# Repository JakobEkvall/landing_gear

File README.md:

# landing_gear
PCB for the Shafter quadrotor landing platforms stepper motor and limit switches. 

Schematics and PCB designed with KiCad. 

Mouser cart for the needed components: https://www.mouser.se/ProjectManager/ProjectDetail.aspx?AccessID=22832bf478

The core of the circuit is an Atmega328P, set up in the same way as the Arduino Nano MCU with a USB connection. 

Stepper motor is driven with a DRV8825 IC.

Limit switches are active LOW.

The whole circuit is powered with a battery, minimum input voltage should be around 8V (otherwise the stepper motor driver will not work) and the maximum battery voltage should not exceed 15V, otherwise the 5V regulator could be damaged. Heatsinks might be needed for the stepper driver IC and the 5V regulator, depending on the input battery voltage and the power consumption of the stepper motor. 

Two resistors on the PCB, R3 and R4, do not have values as that depends on the specific model of  stepper motor used and other factors, see section 8.3.2 in the datasheet for further information on resistor value selection https://www.ti.com/lit/ds/symlink/drv8825.pdf?ts=1690949266854&ref_url=https%253A%252F%252Fwww.ti.com%252Fproduct%252FDRV8825. 

 All of the digital pins on the stepper motor IC are routed to pins on the microcontroller, so MODE and DECAY etc will have to be defined in code and is not preset.

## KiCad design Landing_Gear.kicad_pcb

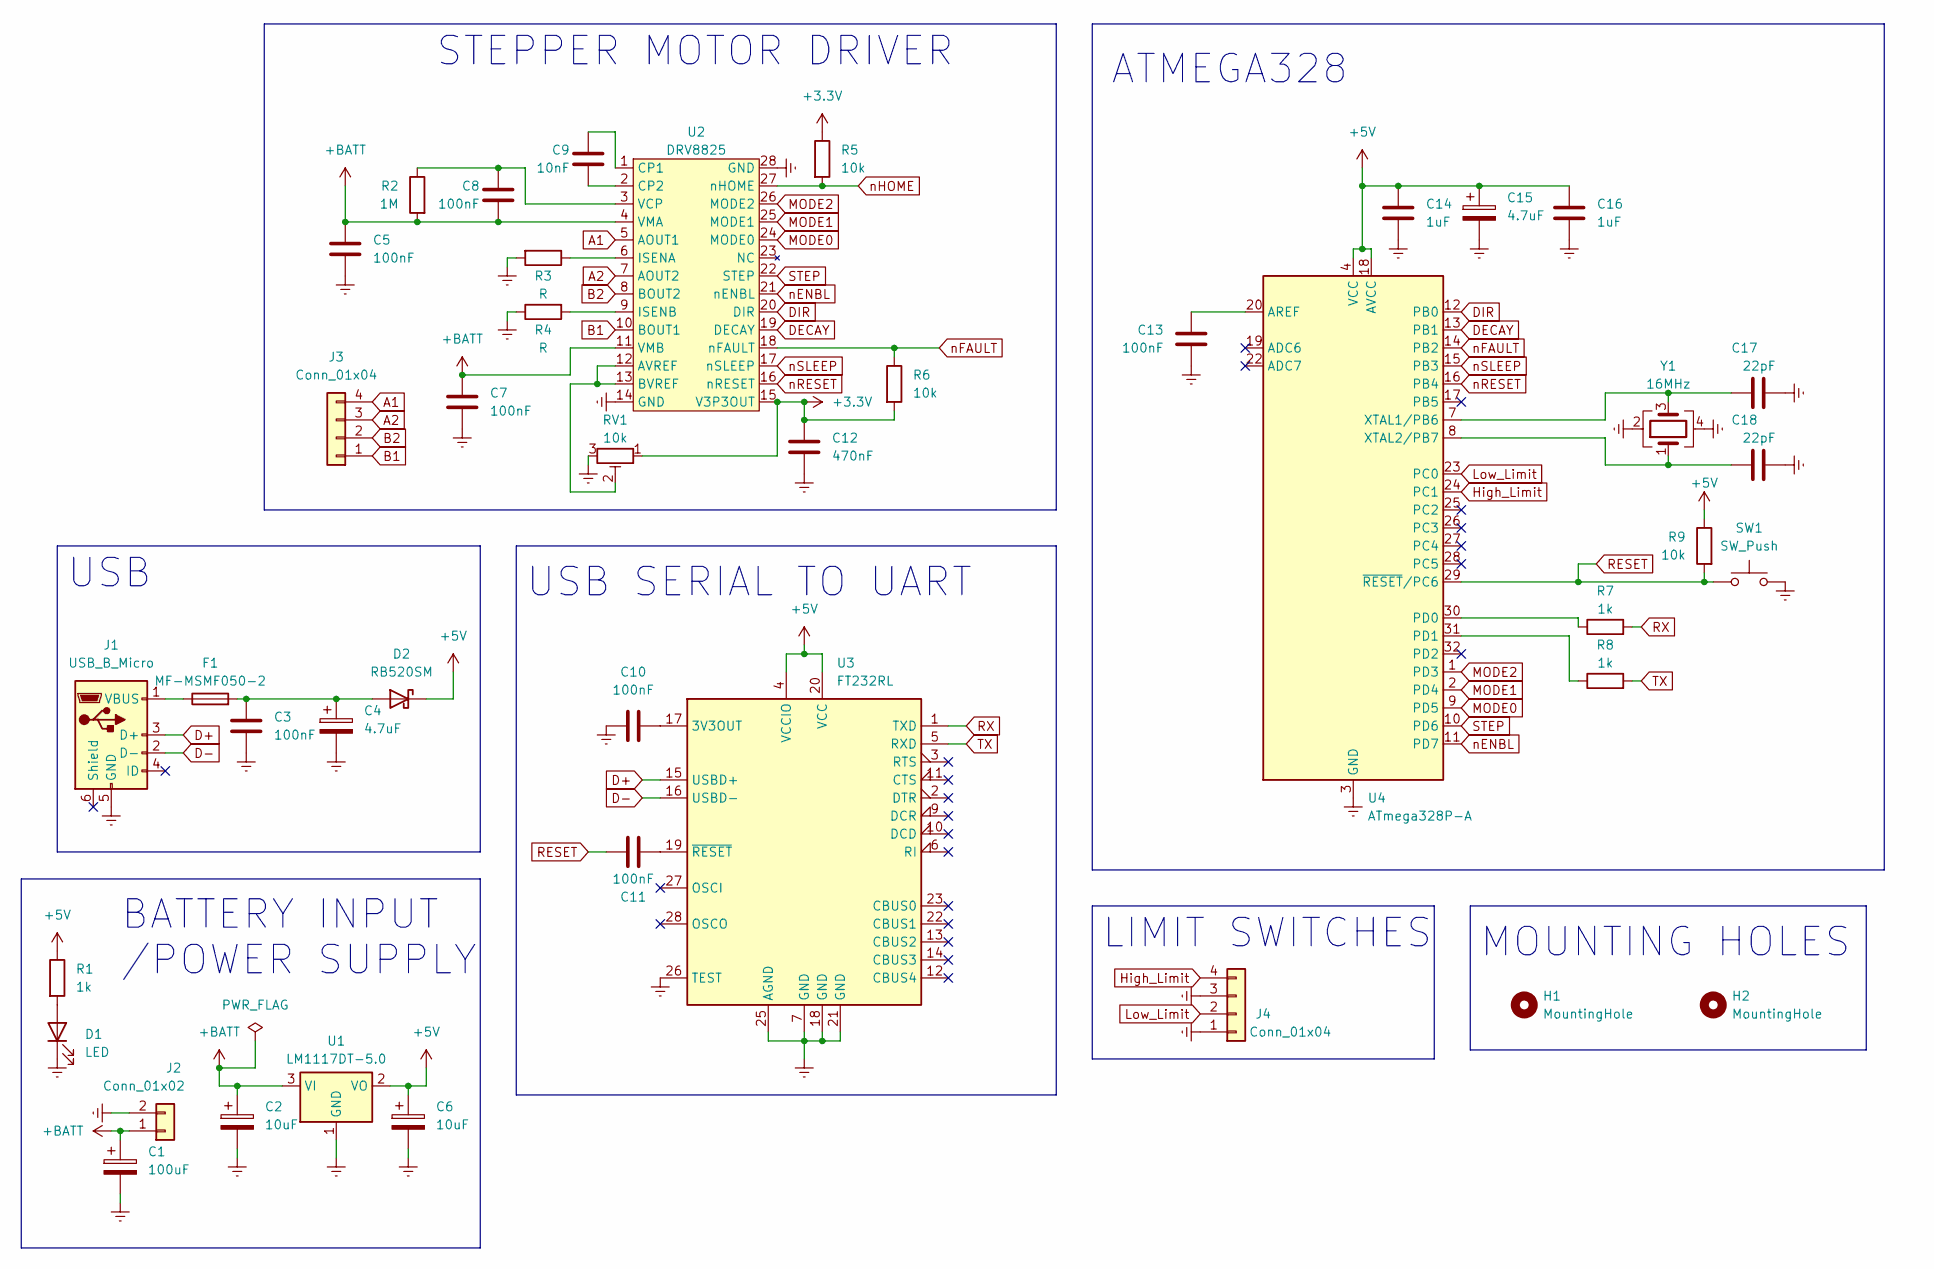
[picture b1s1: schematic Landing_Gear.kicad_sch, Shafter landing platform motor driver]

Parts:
C1: 100uF; CP_Elec_4x4.5
C2, C6: 10uF; CP_Elec_4x4.5
C3, C5, C7, C8, C10, C11, C13: 100nF; C_0603_1608Metric
C4, C15: 4.7uF; CP_Elec_4x4.5
C9: 10nF; C_0603_1608Metric
C12: 470nF; C_0603_1608Metric
C14, C16: 1uF; C_0603_1608Metric
C17, C18: 22pF; C_0603_1608Metric
D1: LED; LED_0805_2012Metric
D2: RB520SM; D_SOD-523
F1: MF-MSMF050-2; Fuse_1812_4532Metric
H1, H2: MountingHole; MountingHole_3.2mm_M3
J1: USB_B_Micro; USB_Micro-B_GCT_USB3076-30-A
J2: Conn_01x02; Battery holes
J3, J4: Conn_01x04; PinHeader_1x04_P2.54mm_Vertical
R1, R7, R8: 1k; R_0603_1608Metric
R2: 1M; R_0603_1608Metric
R3, R4: R; R_0603_1608Metric
R5, R6, R9: 10k; R_0603_1608Metric
RV1: 10k; Potentiometer_Bourns_3314J_Vertical
SW1: SW_Push; SW_SPST_Omron_B3FS-100xP
U1: LM1117DT-5.0; TO-252-3_TabPin2
U2: DRV8825
U3: FT232RL; SSOP-28_5.3x10.2mm_P0.65mm
U4: ATmega328P-A; TQFP-32_7x7mm_P0.8mm
Y1: 16MHz; Crystal_SMD_3225-4Pin_3.2x2.5mm

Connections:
+3.3V: C12.1, R5.1, R6.2, RV1.1, U2.15 (V3P3OUT)
+5V: C6.1, C14.1, C15.1, C16.1, D2.1 (K), R1.1, R9.1, U1.2 (VO), U3.4 (VCCIO), U3.20 (VCC), U4.4 (VCC), U4.6 (VCC), U4.18 (AVCC)
+BATT: C1.1, C2.1, C5.1, C7.1, C8.2, J2.1, R2.2, U1.3 (VI), U2.4 (VMA), U2.11 (VMB)
A1: J3.4, U2.5 (AOUT1)
A2: J3.3, U2.7 (AOUT2)
B1: J3.1, U2.10 (BOUT1)
B2: J3.2, U2.8 (BOUT2)
D+: J1.3 (D+), U3.15 (USBD+)
D-: J1.2 (D-), U3.16 (USBD-)
DECAY: U2.19 (DECAY), U4.13 (PB1)
DIR: U2.20 (DIR), U4.12 (PB0)
Earth: C1.2, C2.2, C3.2, C4.2, C5.2, C6.2, C7.2, C10.1, C12.2, C13.2, C14.2, C15.2, C16.2, C17.2, C18.2, D1.1 (K), J1.5 (GND), J2.2, J4.1, J4.3, R3.2, R4.1, RV1.3, SW1.2, U1.1 (GND), U2.14 (GND), U2.28 (GND), U3.7 (GND), U3.18 (GND), U3.21 (GND), U3.25 (AGND), U3.26 (TEST), U4.3 (GND), U4.5 (GND), U4.21 (GND), Y1.2, Y1.4
High_Limit: J4.4, U4.24 (PC1)
Low_Limit: J4.2, U4.23 (PC0)
MODE0: U2.24 (MODE0), U4.9 (PD5)
MODE1: U2.25 (MODE1), U4.2 (PD4)
MODE2: U2.26 (MODE2), U4.1 (PD3)
unnamed: D1.2 (A), R1.2
unnamed: C3.1, C4.1, D2.2 (A), F1.2
unnamed: F1.1, J1.1 (VBUS)
unnamed: RV1.2, U2.12 (AVREF), U2.13 (BVREF)
unnamed: C9.1, U2.1 (CP1)
unnamed: C9.2, U2.2 (CP2)
unnamed: R3.1, U2.6 (ISENA)
unnamed: R4.2, U2.9 (ISENB)
unnamed: C8.1, R2.1, U2.3 (VCP)
unnamed: C10.2, U3.17 (3V3OUT)
unnamed: C11.2, U3.19 (~RESET)
unnamed: C13.1, U4.20 (AREF)
unnamed: R7.1, U4.30 (PD0)
unnamed: R8.1, U4.31 (PD1)
unnamed: C17.1, U4.7 (XTAL1/PB6), Y1.3
unnamed: C18.1, U4.8 (XTAL2/PB7), Y1.1
RESET: C11.1, R9.2, SW1.1, U4.29 (~RESET/PC6)
RX: R7.2, U3.1 (TXD)
STEP: U2.22 (STEP), U4.10 (PD6)
TX: R8.2, U3.5 (RXD)
nENBL: U2.21 (nENBL), U4.11 (PD7)
nFAULT: R6.1, U2.18 (nFAULT), U4.14 (PB2)
nHOME: R5.2, U2.27 (nHOME)
nRESET: U2.16 (nRESET), U4.16 (PB4)
nSLEEP: U2.17 (nSLEEP), U4.15 (PB3)

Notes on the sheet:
LIMIT SWITCHES
USB
USB SERIAL TO UART
ATMEGA328
MOUNTING HOLES
STEPPER MOTOR DRIVER
BATTERY INPUT /POWER SUPPLY

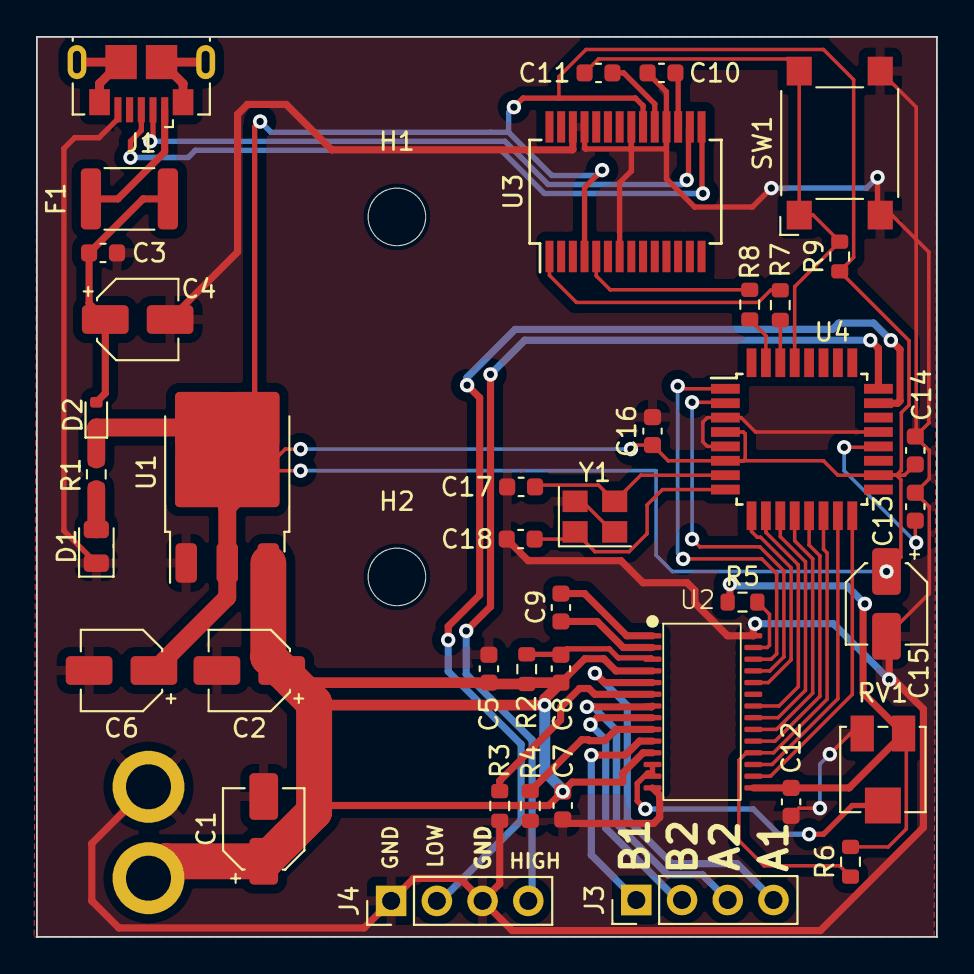
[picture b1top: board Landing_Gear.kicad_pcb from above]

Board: 2 copper layers, 50.0 x 50.0 mm, 43 parts (1 on the bottom side), 42 nets.
